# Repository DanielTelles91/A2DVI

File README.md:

# A2DVI - Apple II Digital Video

This is a project for a digital DVI/HDMI Apple II video card.
It directly produces a digital video stream from Apple II's memory content.
The signal is output via an HDMI connector, connecting the Apple II to modern displays with HDMI (or DVI) inputs.
No more analog signal conversion required.

The project is a collaboration with Thorsten Brehm. His related firmware project is here: https://github.com/ThorstenBr/A2DVI-Firmware

For the DVI output to be active, the new firmware developed by Thorsten should be used.

The card also has an alternative analog VGA connector.
For the VGA output to be active, the [VGA firmware](https://github.com/markadev/AppleII-VGA) developed by Mark Aikens should be used.

The card can produce either an analog VGA or a digital HDMI signal, but not both simultaneously.
To switch between modes, a firmware update is required and opening/closing connections.

## Dual-Language Support
The pin on the v1.5 and later boards is for AltChr connection, supported by A2DVI firmware for switching between alternative character sets on non-US versions of Apple II ("Euro-machines").

# Hardware
* Based on the PICO controller board.
* Provides a DVI video stream via an HDMI connector.
* Low power/heat dissipation: less than 70mA@5V = 0.35W in operation.
* Uses 4x 74LV245 bus transceivers for 5V/3.3V signal conversion of the Apple II bus.
* Separate ALTCHR input pin for dual-language support: pin needs to be wired separately to the "language switch" of Euro-Apple IIs (optional).

# Thanks
This is a project based on:

* the AppleII-VGA project by Mark Aikens - https://github.com/markadev/AppleII-VGA

* the PicoDVI project by Luke Wren - https://github.com/Wren6991/PicoDVI

* Thorsten Brehm for firmware development and board design considerations

* Oliver Schmidt on original idea discussions and design considerations

# License
Board design by Ralle Palaveev (c) 2024.

All rights reserved.

Redistribution and use in source, binary, and manufactured forms, with or without
modification, are permitted provided that the following conditions are met:
1. Redistributions of source code and design files must retain the above copyright
   notice, this list of conditions and the following disclaimer.
2. Redistributions in binary or manufactured form must reproduce the above copyright
   notice, this list of conditions and the following disclaimer in the
   documentation and/or other materials provided with the distribution.
3. All advertising materials mentioning features or use of this software
   or hardware must display the following acknowledgement:
   This product includes software or hardware developed by Ralle Palaveev.
4. Neither the name of Ralle Palaveev nor the
   names of its contributors may be used to endorse or promote products
   derived from this software or hardware without specific prior written permission.

The above copyright notice and this permission notice shall be included in all
copies or substantial portions of the Software.

THE SOFTWARE IS PROVIDED "AS IS", WITHOUT WARRANTY OF ANY KIND, EXPRESS OR
IMPLIED, INCLUDING BUT NOT LIMITED TO THE WARRANTIES OF MERCHANTABILITY,
FITNESS FOR A PARTICULAR PURPOSE AND NONINFRINGEMENT. IN NO EVENT SHALL THE
AUTHORS OR COPYRIGHT HOLDERS BE LIABLE FOR ANY CLAIM, DAMAGES OR OTHER
LIABILITY, WHETHER IN AN ACTION OF CONTRACT, TORT OR OTHERWISE, ARISING FROM,
OUT OF OR IN CONNECTION WITH THE SOFTWARE OR THE USE OR OTHER DEALINGS IN THE
SOFTWARE.

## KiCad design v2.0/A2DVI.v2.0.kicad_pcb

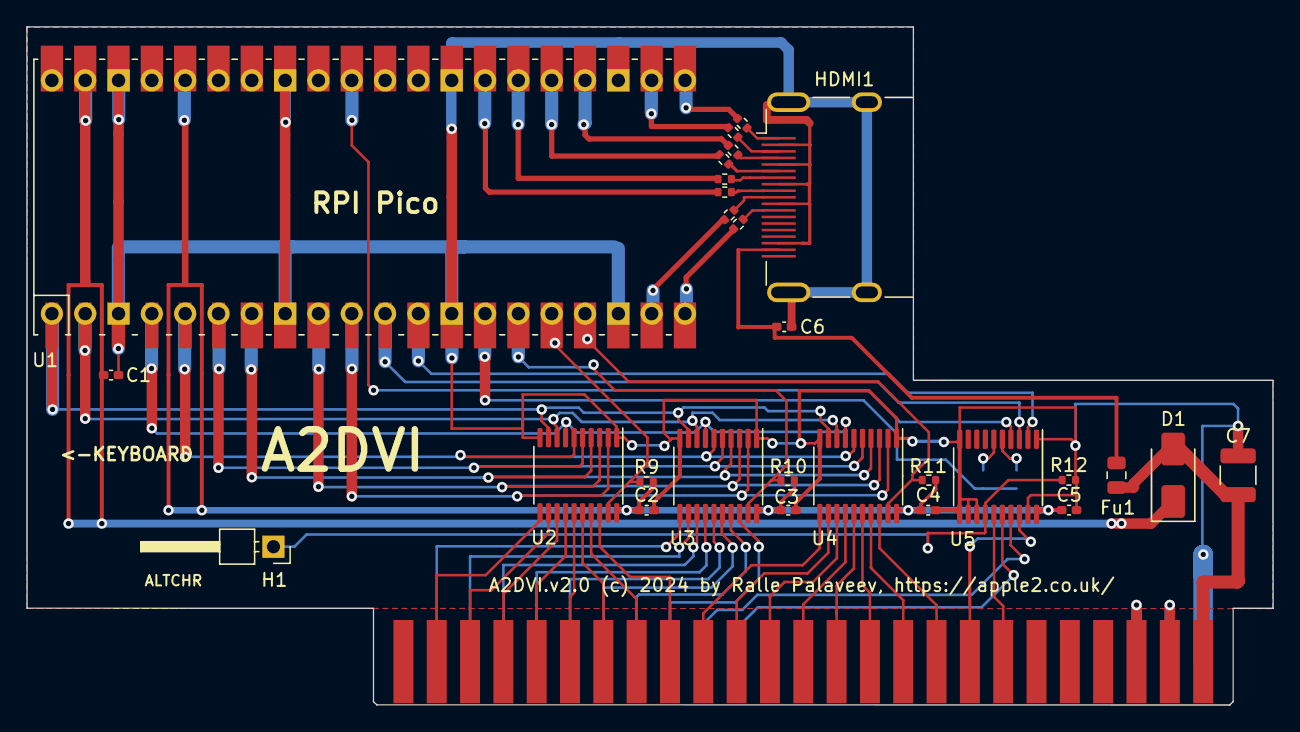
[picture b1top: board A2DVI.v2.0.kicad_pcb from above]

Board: 2 copper layers, 95.0 x 51.7 mm, 28 parts (0 on the bottom side), 29 nets.

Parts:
C1, C2, C3, C4, C5, C6: 100n; C_0402_1005Metric_Pad0.74x0.62mm_HandSolder
C7: C_1210_3225Metric
D1: SS16; D_SMA
Fu1: Fuse_0805_2012Metric
H1: PinHeader_1x01_P2.54mm_Horizontal
HDMI1: HDMI_A_Molex_208658-1001_Horizontal
R1, R2, R3, R4, R5, R6, R7, R8: 270; R_0402_1005Metric
R9, R10, R11, R12: 10k; R_0402_1005Metric
U1: Pico; RPi_PicoW_SMD_TH
U2, U3, U4, U5: SN74LVC245APWR; TSSOP-20_4.4x6.5mm_P0.65mm

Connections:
3.3V: C2.1, C3.1, C4.1, C5.1, R9.2, R10.2, R11.2, U1.36 (3V3), U2.20, U3.20, U4.20, U5.20
5V: C7.2, D1.2, Fu1.2
5V_out: C6.1, Fu1.1, HDMI1.18
AD0: U1.1 (GPIO0), U2.9, U3.9, U4.9
AD1: U1.2 (GPIO1), U2.8, U3.8, U4.8
AD2: U1.4 (GPIO2), U2.7, U3.7, U4.7
AD3: U1.5 (GPIO3), U2.6, U3.6, U4.6
AD4: U1.6 (GPIO4), U2.5, U3.5, U4.5
AD5: U1.7 (GPIO5), U2.4, U3.4, U4.4
AD6: U1.9 (GPIO6), U2.3, U3.3, U4.3
AD7: U1.10 (GPIO7), U2.2, U3.2, U4.2
Altchr: H1.1, R12.1, U5.14
CK_N: R8.1, U1.20 (GPIO15)
CK_P: R7.1, U1.19 (GPIO14)
D0_N: R6.1, U1.27 (GPIO21)
D0_P: R5.1, U1.26 (GPIO20)
D1_N: R4.1, U1.25 (GPIO19)
D1_P: R3.1, U1.24 (GPIO18)
D2_N: R2.1, U1.22 (GPIO17)
D2_P: R1.1, U1.21 (GPIO16)
D2_otut_P: HDMI1.1, R1.2
DATAOE: R10.1, U1.15 (GPIO11), U3.19
GND: C1.2, C2.2, C3.2, C4.2, C5.2, C6.2, C7.1, HDMI1.2, HDMI1.5, HDMI1.8, HDMI1.11, HDMI1.17, HDMI1.SH, R12.2, U1.3 (GND), U1.8 (GND), U1.13 (GND), U1.18 (GND), U1.23 (GND), U1.28 (GND), U1.33 (AGND), U1.38 (GND), U2.1, U2.10, U3.1, U3.10, U4.1, U4.10, U5.1, U5.10, U5.11, U5.12, U5.13, U5.19
L-DevSel: U1.11 (GPIO8), U5.3
L-PHI0: U1.31 (GPIO26_ADC0), U5.4
L-RW: U1.12 (GPIO9), U5.2
LSBOE: R9.1, U1.16 (GPIO12), U2.19
MSBOE: R11.1, U1.17 (GPIO13), U4.19
VSYS: C1.1, D1.1, U1.39 (VSYS)

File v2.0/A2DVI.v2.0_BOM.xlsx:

Comment | Designator | Footprint | JLCPCB Part #（optional）
HDMI connector | HDMI1 |  | C7501808
PinHeader_1x01_P2.54mm_Horizontal | H1 |  | C2883838
270 | R1,R2,R3,R4,R5,R6,R7,R8 | 0402 | C25099
10k | R9,R10,R11,R12 | 0402 | C25744
16V 100nF X7R ±10% 0402 Multilayer Ceramic Capacitors MLCC - SMD/SMT ROHS | C1,C2,C3,C4,C5,C6 | 0402 | C1525
10V 100uF X5R ±20% 1210 Multilayer Ceramic Capacitors MLCC - SMD/SMT ROHS | C7 | 1210 | C386065
MBR120VLSFT1G | D1 | SOD123-FL | C223608
6V 100mA Resettable Fuse | Fu1 | 0805 | C20975
Raspberry Pi PICO | U1 |  | C7203002
SN74LVC245APWR | U2,U3,U4,U5 | TSSOP-20 | C7848

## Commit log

2024-10-11 adicionado fotos
2024-10-11 Removido a malha GND

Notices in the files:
v2.0/A2DVI.v2.0.kicad_pcb:
A2DVI.v2.0 (c) 2024 by Ralle Palaveev, https://apple2.co.uk
Board design by R. Palaveev, (c) 2024
Firmware by Thorsten Brehm, (c) 2024
